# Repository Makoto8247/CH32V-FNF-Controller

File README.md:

# CH32V-FNF-Controller
## 概要

CH32V003F4P6を使用しFridayNightFunkinの専用コントローラーを作成しました。
## パーツ
- CH32V003F4P6 * 1
- CH9329 * 1
- ボタン * 8 or 9
- LED * 1
- XHコネクタ * 9
- USB Type-Cコネクタ * 1
- リセッタブルヒューズ 500mA * 1
- コンデンサ 0.1μF * 3
- 抵抗
  - 5k1 * 1
  - 10k * 7
  - 200 * 1
## マイコン
CH32V003F4P6用に設計しており、MounRiverを使用しています。  
他のマイコンを使用する場合、mainファイルの書き換えやPCBデータの書き換えが必要になる場合があります。
## PCB
ソフトウェアはKiCadを使用しています。  
outputフォルダに既にガーバーデータを出力したファイルを格納しているのでそこから基盤を作成しても構いません。しかし、初めて基盤を作成したので不具合がある可能性があります。  
スペース用のボタンは2つ使えるようにしていますが、1つのみでも使えるようにしています。

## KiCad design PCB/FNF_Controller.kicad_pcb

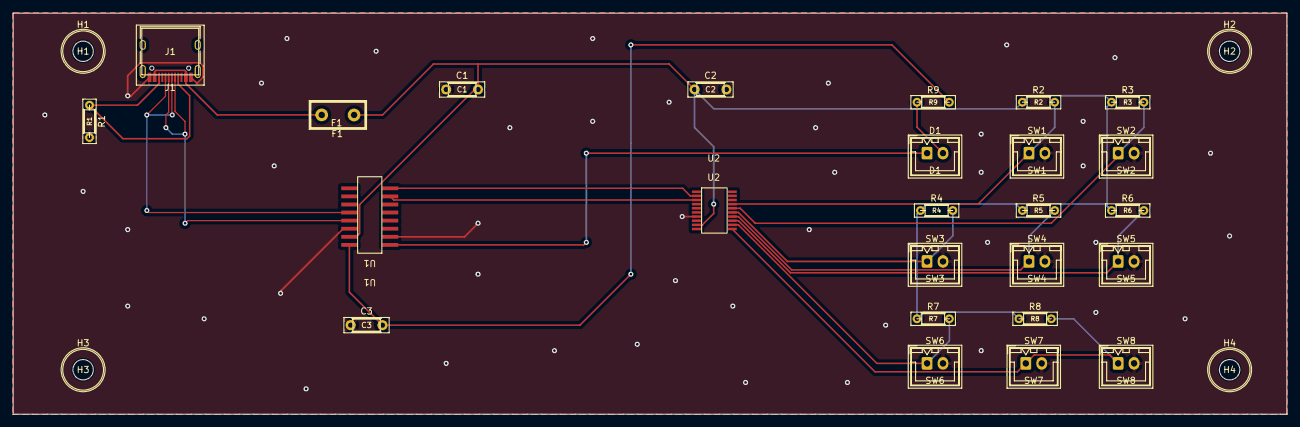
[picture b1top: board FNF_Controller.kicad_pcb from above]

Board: 2 copper layers, 200.0 x 63.0 mm, 29 parts (0 on the bottom side), 18 nets.

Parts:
C1, C2, C3: 0.1μF; C_Disc_D4.3mm_W1.9mm_P5.00mm
D1: LED; JST_XH_B2B-XH-A_1x02_P2.50mm_Vertical
F1: 500mA; Fuse_Littelfuse_395Series
H1, H2, H3, H4: MountingHole; MountingHole_3.2mm_M3
J1: USB_C_Receptacle_USB2.0; USB_C_Receptacle_HRO_TYPE-C-31-M-12
R1: 5k1; R_Axial_DIN0204_L3.6mm_D1.6mm_P5.08mm_Horizontal
R2, R3, R4, R5, R6, R7, R8: 10k; R_Axial_DIN0204_L3.6mm_D1.6mm_P5.08mm_Horizontal
R9: 3k3; R_Axial_DIN0204_L3.6mm_D1.6mm_P5.08mm_Horizontal
SW1: LEFT_ARROW; JST_XH_B2B-XH-A_1x02_P2.50mm_Vertical
SW2: DOWN_ARROW; JST_XH_B2B-XH-A_1x02_P2.50mm_Vertical
SW3: UP_ARROW; JST_XH_B2B-XH-A_1x02_P2.50mm_Vertical
SW4: RIGHT_ARROW; JST_XH_B2B-XH-A_1x02_P2.50mm_Vertical
SW5: ENTER_KEY; JST_XH_B2B-XH-A_1x02_P2.50mm_Vertical
SW6: ESC_KEY; JST_XH_B2B-XH-A_1x02_P2.50mm_Vertical
SW7: SPACE1; JST_XH_B2B-XH-A_1x02_P2.50mm_Vertical
SW8: SPACE2; JST_XH_B2B-XH-A_1x02_P2.50mm_Vertical
U1: ch9329
U2: ch32v003f4p6

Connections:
D+: J1.A6 (D+), J1.B6 (D+), U1.12 (UD+)
D-: J1.A7 (D-), J1.B7 (D-), U1.13 (UD-)
GNDREF: C1.1, C2.2, C3.1, J1.A1 (GND), J1.A12 (GND), J1.B1 (GND), J1.B12 (GND), R1.2, SW1.2 (A), SW2.2 (A), SW3.2 (A), SW4.2 (A), SW5.2 (A), SW6.2 (A), SW7.2 (A), SW8.2 (A), U1.2 (MODE0), U1.14 (GND), U2.7 (VSS)
unnamed: D1.2 (A), R9.1
unnamed: D1.1 (K), U1.1 (ACT#)
unnamed: J1.A5 (CC1), J1.B5 (CC2), R1.1
unnamed: F1.2, J1.A4 (VBUS), J1.A9 (VBUS), J1.B4 (VBUS), J1.B9 (VBUS)
unnamed: U1.8 (RXD), U2.2 (PD5/UTX)
unnamed: U1.7 (TXD), U2.3 (PD6/URX)
unnamed: C3.2, R9.2, U1.16 (V33)
unnamed: C1.2, C2.1, F1.1, R2.1, R3.1, R4.1, R5.1, R6.1, R7.1, R8.1, U1.15 (VCC), U2.9 (VDD)
unnamed: R8.2, SW7.1 (A), SW8.1 (A), U2.11 (PC1)
unnamed: R7.2, SW6.1 (A), U2.12 (PC2)
unnamed: R6.2, SW5.1 (A), U2.13 (PC3)
unnamed: R5.2, SW4.1 (A), U2.14 (PC4)
unnamed: R4.2, SW3.1 (A), U2.15 (PC5)
unnamed: R3.2, SW2.1 (A), U2.16 (PC6)
unnamed: R2.2, SW1.1 (A), U2.17 (PC7)

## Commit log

2023-08-20 Add MicroController README.md
